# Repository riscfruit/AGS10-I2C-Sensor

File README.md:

# AGS10-I2C-Sensor
Riscfruit Aosong AGS10 Air Quality I2C sensor module

### Gallery

### License
Copyright (c) 2026, Riscfruit Laboratory. This open source hardware is released under [CERN-OHL-S-2.0](LICENSE).

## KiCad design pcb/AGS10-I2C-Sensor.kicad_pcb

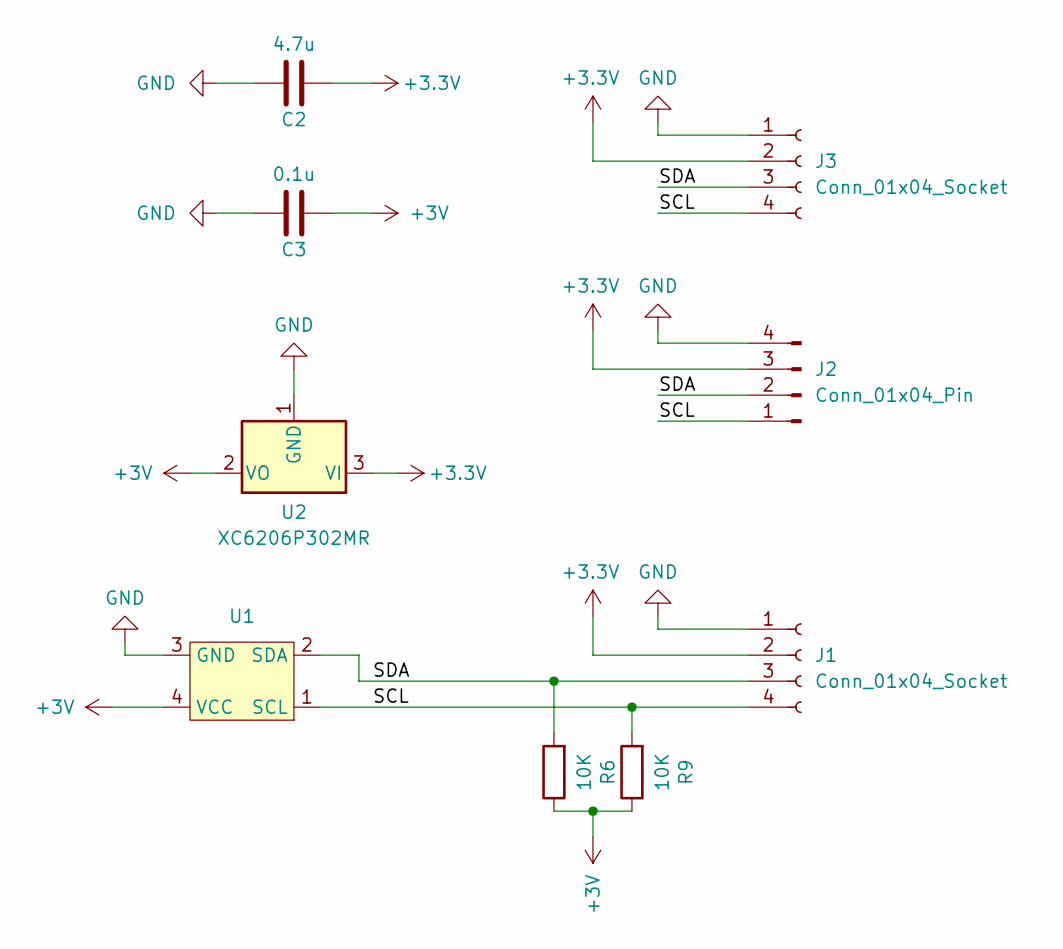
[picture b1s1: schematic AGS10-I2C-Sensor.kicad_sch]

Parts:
C2: 4.7u; C_0402_1005Metric
C3: 0.1u; C_0402_1005Metric
J1, J3: Conn_01x04_Socket; JST_SH_SM04B-SRSS-TB_1x04-1MP_P1.00mm_Horizontal
J2: Conn_01x04_Pin; PinHeader_1x04_P2.54mm_Vertical
R6, R9: 10K; R_0402_1005Metric
U1: SENSOR-SMD_AGS10
U2: XC6206P302MR; SOT-23

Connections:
+3.3V: C2.1, J1.2, J2.3, J3.2, U2.3 (VI)
+3V: C3.1, R6.1, R9.1, U1.4 (VCC), U2.2 (VO)
/SCL: J1.4, J2.1, J3.4, R9.2, U1.1 (SCL)
/SDA: J1.3, J2.2, J3.3, R6.2, U1.2 (SDA)
GND: C2.2, C3.2, J1.1, J2.4, J3.1, U1.3 (GND), U2.1 (GND)

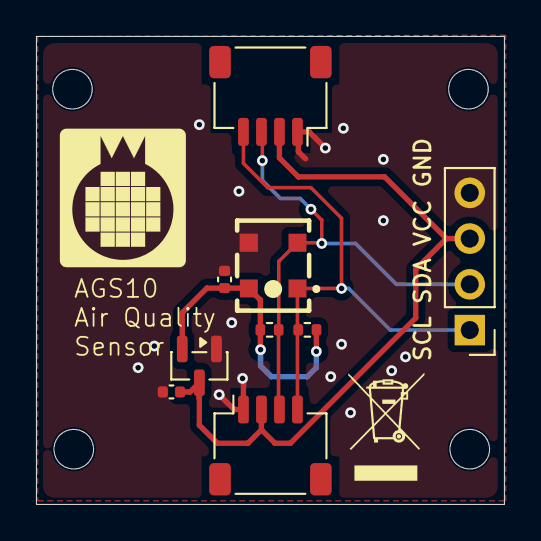
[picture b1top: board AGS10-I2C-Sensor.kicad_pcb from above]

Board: 2 copper layers, 26.0 x 26.0 mm, 13 parts (0 on the bottom side), 5 nets.

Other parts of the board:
H1, H1#2, H1#3, H1#4: MountingHole; MountingHole_2.2mm_M2
